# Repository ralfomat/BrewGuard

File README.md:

## BrewGuard

BrewGuard is a Smart Coffee Access & Analytics System. A solution that transforms regular coffee machines into smart, trackable brewing stations using RFID authentication and real-time monitoring. This system combines hardware and software components to manage coffee machine access and track usage.

## Key Features

-   RFID-based authentication system for secure coffee machine access    
-   User permission management and access tracking
-   Support for multiple RFID tags and users
- User based tracking of coffee consumption

## Technical Stack

**Hardware**

-   RaspberryPi Pico based RFID reader integration
-   Coffee machine interface with Relay output
- 0.96" OLED Display
- Responsive UI

**Software**

-  Firmware written in MicroPython
-  PCBs designed in KICAD

This project is perfect for offices, shared workspaces, and environments where coffee consumption tracking and access control are essential.

## PCB Design

BrewGuard Mainboard v0.1

BrewGuard Keyboard v0.1

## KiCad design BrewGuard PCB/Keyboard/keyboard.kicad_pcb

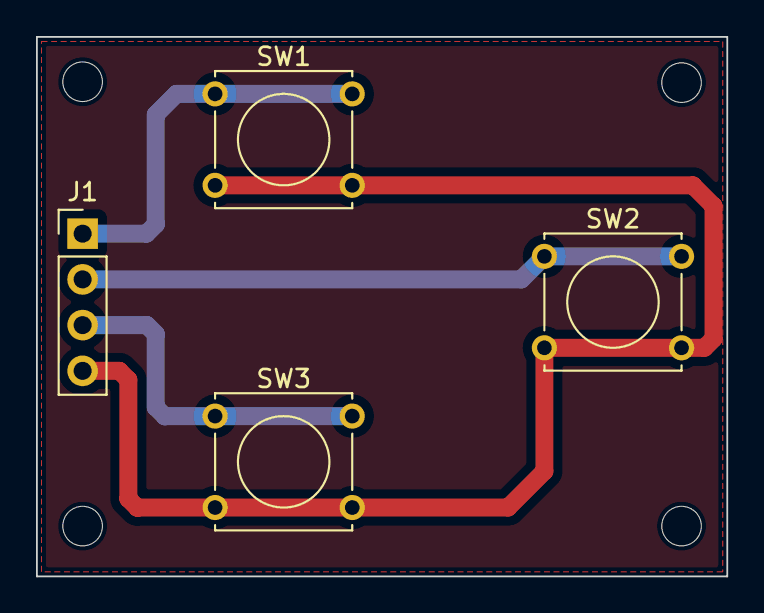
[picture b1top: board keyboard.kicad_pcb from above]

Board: 2 copper layers, 38.4 x 30.0 mm, 8 parts (0 on the bottom side), 4 nets.

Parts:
H1, H2, H3, H4: MountingHole; MountingHole_2.2mm_M2_DIN965
J1: Tasterplatine; PinHeader_1x04_P2.54mm_Vertical
SW1, SW2, SW3: SW_Push; SW_Tactile_Straight_KSA0Axx1LFTR

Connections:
/5VB: J1.4, SW1.2, SW2.2, SW3.2
unnamed: J1.1, SW1.1
unnamed: J1.2, SW2.1
unnamed: J1.3, SW3.1

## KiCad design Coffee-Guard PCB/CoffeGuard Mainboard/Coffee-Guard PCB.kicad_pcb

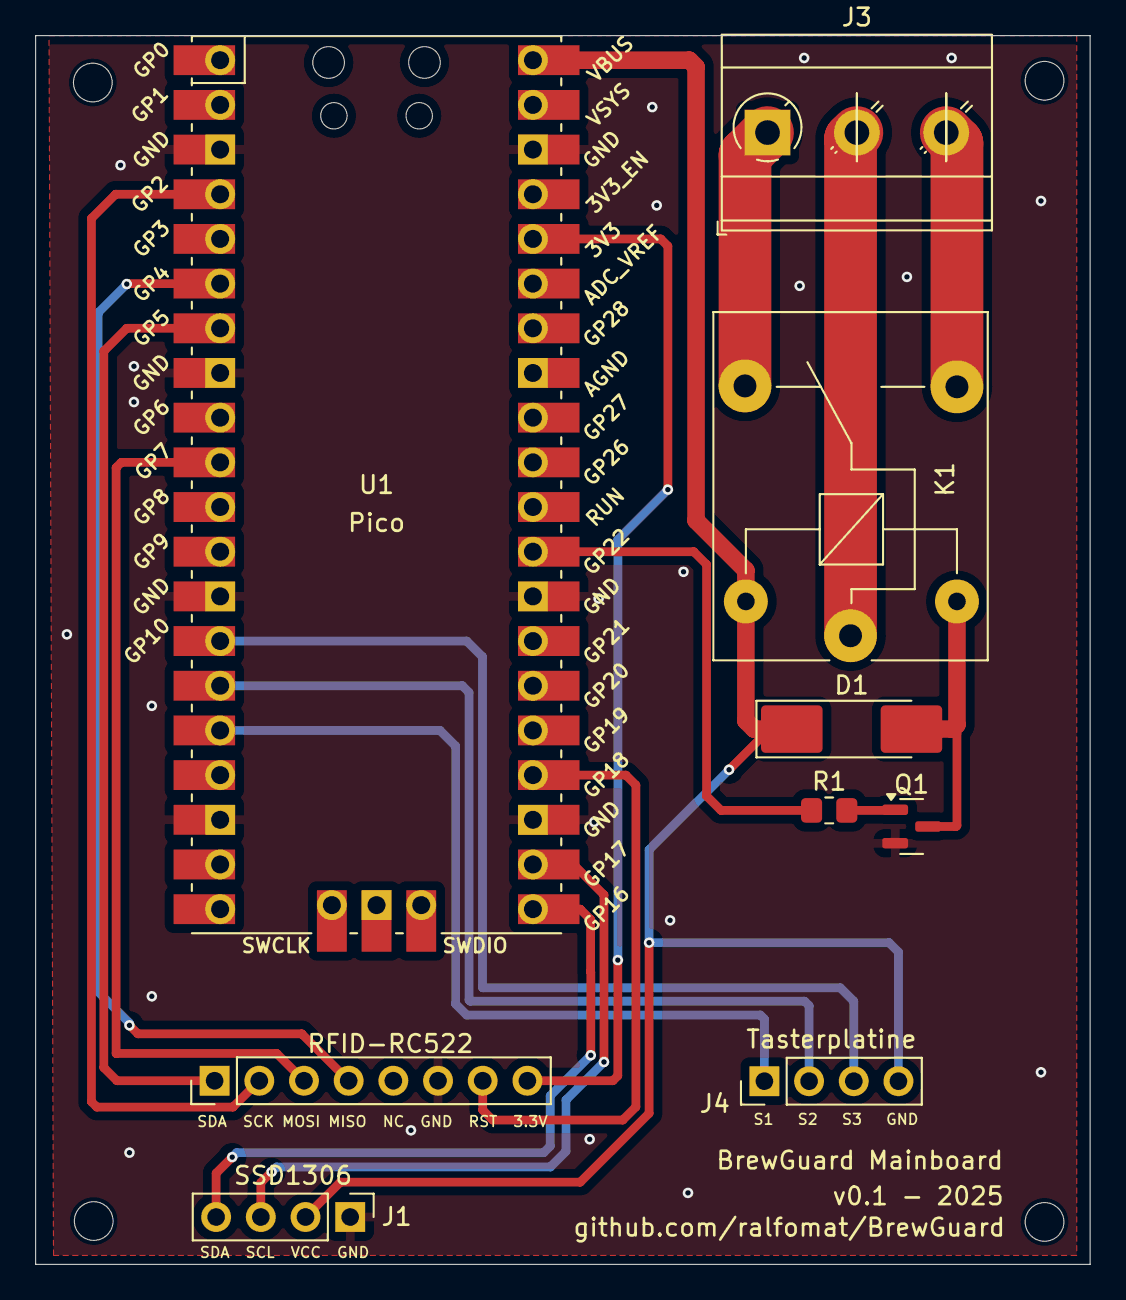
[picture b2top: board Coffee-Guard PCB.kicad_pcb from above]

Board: 2 copper layers, 59.9 x 69.8 mm, 13 parts (0 on the bottom side), 19 nets.

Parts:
D1: D; D_MELF_Handsoldering
H1, H2, H3, H4: MountingHole; MountingHole_2.2mm_M2_DIN965
J1: SSD1306; PinHeader_1x04_P2.54mm_Vertical
J2: RFID-RC522; PinHeader_1x08_P2.54mm_Vertical
J3: Relay Output; TerminalBlock_MetzConnect_Type073_RT02603HBLU_1x03_P5.08mm_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
J4: Tasterplatine; PinHeader_1x04_P2.54mm_Vertical
K1: SANYOU_SRD_Form_C; Relay_SPDT_SANYOU_SRD_Series_Form_C
Q1: BC847; SOT-23
R1: 1000R; R_0805_2012Metric_Pad1.20x1.40mm_HandSolder
U1: Pico; RPi_Pico_SMD_TH

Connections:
/3.3V: J2.8, U1.36 (3V3)
/11: J3.2, K1.1
/12: J3.1, K1.4
/14: J3.3, K1.3
/GND: J1.1, J2.6, Q1.2 (E), U1.3 (GND), U1.8 (GND), U1.13 (GND), U1.18 (GND), U1.23 (GND), U1.28 (GND), U1.38 (GND)
/MISO: J2.4, U1.6 (GPIO4)
/MOSI: J2.3, U1.10 (GPIO7)
/RST: J2.7, U1.24 (GPIO18)
/SCK: J2.2, U1.4 (GPIO2)
/SCL: J1.3, U1.22 (GPIO17)
/SDA_1: J1.4, U1.21 (GPIO16)
/SDA_2: J2.1, U1.7 (GPIO5)
/VCC: D1.1 (K), J1.2, J4.4, K1.5, U1.40 (VBUS)
unnamed: D1.2 (A), K1.2, Q1.3 (C)
unnamed: J4.1, U1.16 (GPIO12)
unnamed: J4.2, U1.15 (GPIO11)
unnamed: J4.3, U1.14 (GPIO10)
unnamed: Q1.1 (B), R1.2
unnamed: R1.1, U1.29 (GPIO22)

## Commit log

2025-01-05 new concept 0.1
2025-01-05 bugfixes
2025-01-07 pcb files
2025-01-07 correction
2025-01-07 remove of not required libs
2025-01-07 3d model
2025-01-07 corr.
2025-01-09 add additional options for admin menu
